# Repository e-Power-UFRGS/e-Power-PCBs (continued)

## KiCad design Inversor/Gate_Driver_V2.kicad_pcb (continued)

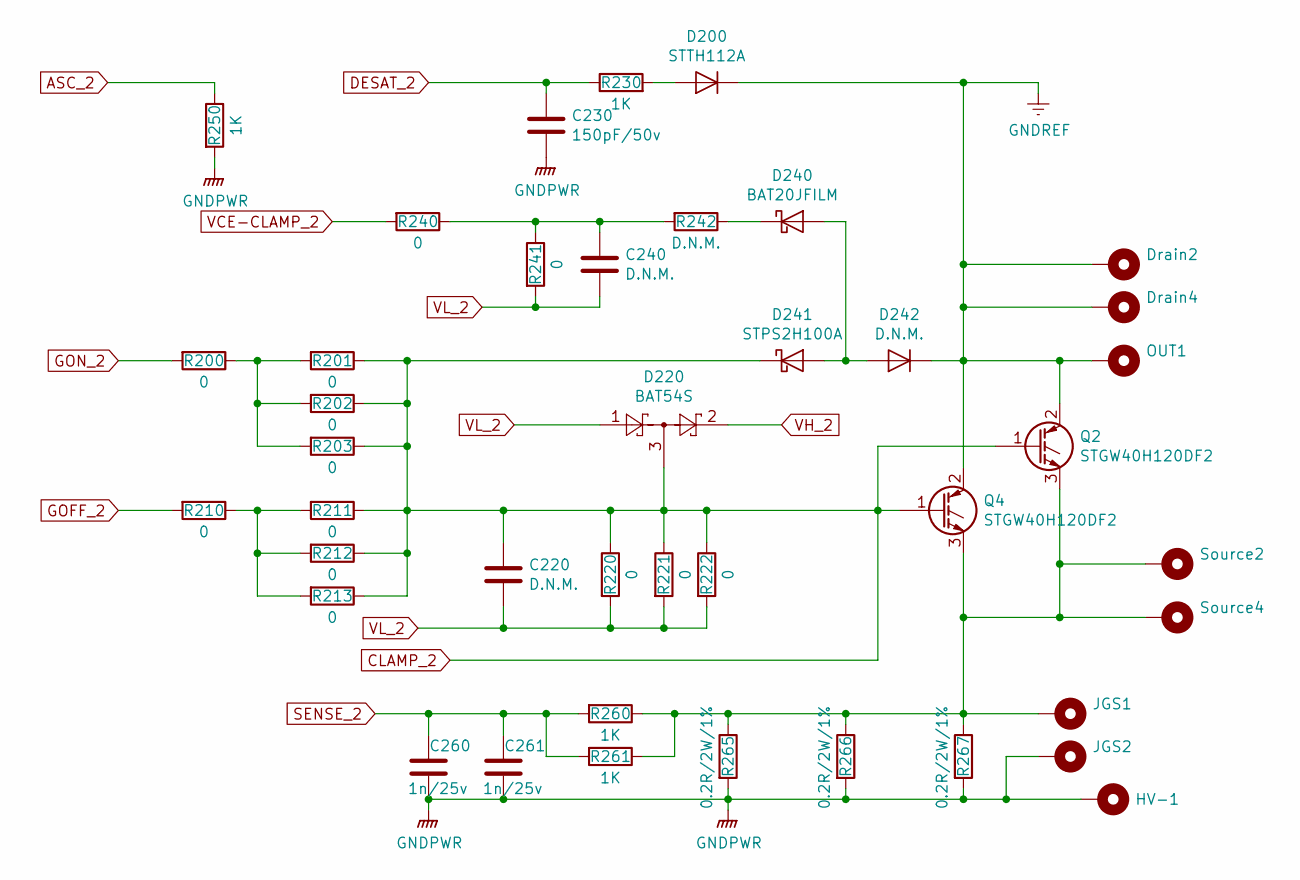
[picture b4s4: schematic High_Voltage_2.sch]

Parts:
C220, C240: D.N.M.; C_0805_2012Metric
C230: 150pF/50v; C_0805_2012Metric
C260, C261: 1n/25v; C_0805_2012Metric
D200: STTH112A; D_SMA
D220: BAT54S; SOT-23
D240: BAT20JFILM; DO-214AC
D241: STPS2H100A; DO-214AC
D242: D.N.M.; D_SMA
Drain2, Drain4: MountingHole_Pad; MountingHole_2.2mm_M2_DIN965_Pad
HV-1: MountingHole_Pad; MountingHole_4.5mm_Pad
JGS1, JGS2: MountingHole_Pad; MountingHole_2.2mm_M2_DIN965_Pad
OUT1: MountingHole_Pad; MountingHole_4.5mm_Pad
Q1, Q2: STGW40H120DF2; TO-247-3_Vertical
R200, R201, R202, R203, R210, R211, R212, R213, R220, R221, R222, R240, R241: 0; R_0805_2012Metric
R230, R250, R260, R261: 1K; R_0805_2012Metric
R242: D.N.M.; R_0805_2012Metric
R265, R266, R267: 0.2R/2W/1%; R_2512_6332Metric
Source2, Source4: MountingHole_Pad; MountingHole_2.2mm_M2_DIN965_Pad

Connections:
ASC_2: R250.1; also elsewhere on the board
DESAT_2: C230.1, R230.1; also elsewhere on the board
GND_ISO_2: C230.2, C260.2, C261.2, HV-1.1, JGS2.1, R250.2, R265.2, R266.2, R267.2; also elsewhere on the board
GOFF_2: R210.2; also elsewhere on the board
GON_2: R200.2; also elsewhere on the board
unnamed: C240.1, R240.1, R241.1, R242.2
unnamed: D240.1 (K), R242.1
unnamed: D240.2 (A), D241.2 (A), D242.2 (A)
unnamed 27: D200.2 (A), R230.2; also elsewhere on the board
unnamed: R200.1, R201.2, R202.2, R203.2
unnamed: R210.1, R211.2, R212.2, R213.2
SENSE_2: C260.1, C261.1, R260.2, R261.2; also elsewhere on the board
VCE-CLAMP_2: R240.2; also elsewhere on the board
VH_2: D220.2; also elsewhere on the board
VL_2: C220.2, C240.2, D220.1, R220.2, R221.2, R222.2, R241.2; also elsewhere on the board

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
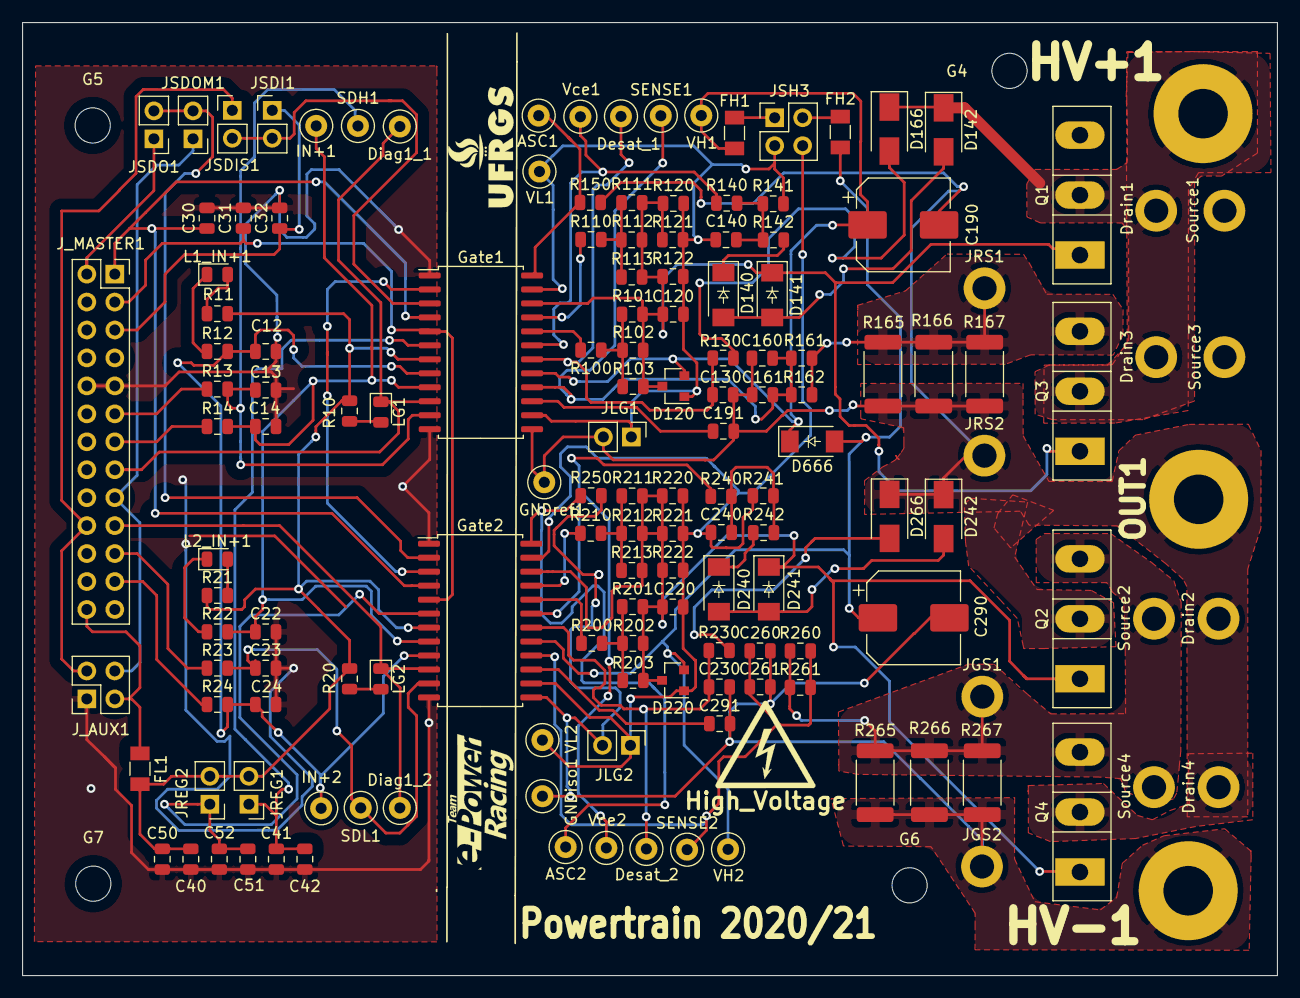
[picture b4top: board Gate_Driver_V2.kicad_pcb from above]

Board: 2 copper layers, 114.0 x 86.6 mm, 158 parts (0 on the bottom side), 69 nets.

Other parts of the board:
D166, D266: STTH112A; D_SMA
Q4: STGW40H120DF2; TO-247-3_Vertical

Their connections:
unnamed 24: D166.2; also elsewhere on the board
unnamed 27: D266.2; also elsewhere on the board

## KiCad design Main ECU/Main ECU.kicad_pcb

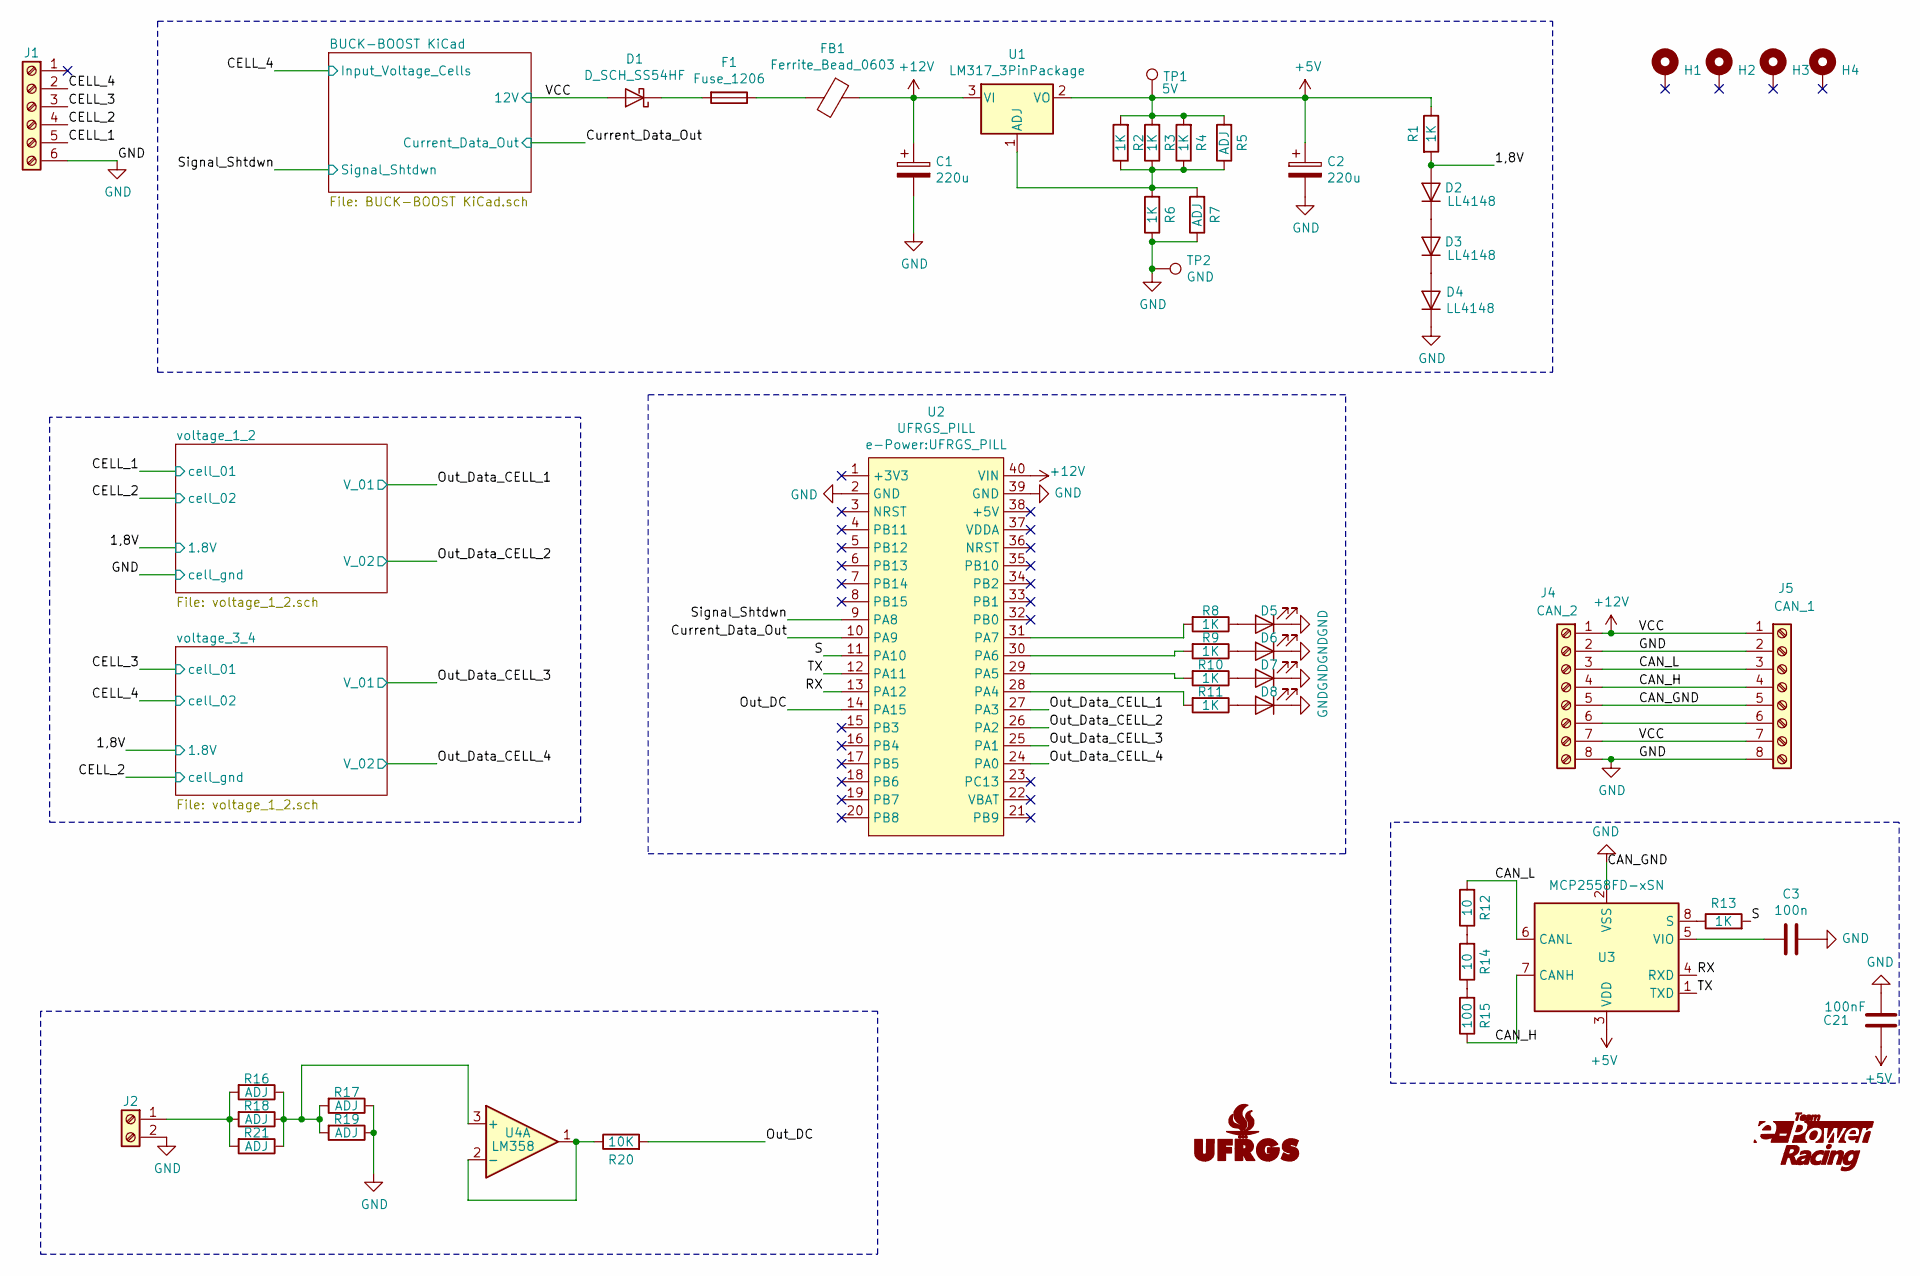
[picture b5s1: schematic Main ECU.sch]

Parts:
C1, C2: 220u; CP_Elec_10x10
C3: 100n; C_0805_2012Metric
C21: 100nF; C_0805_2012Metric
D1: D_SCH_SS54HF; DO-214AC; LCSC C22452
D2, D3, D4: LL4148; SOD-80
D5, D6, D7, D8: LED; LED_0805_1.15x1.40mm_HandSolder
F1: Fuse_1206; FUSE_1206_3216Metric
FB1: Ferrite_Bead_0603; FB_0805_2012Metric
G1: Logo_UFRGS_Large; Logo_UFRGS_14.7x8.0mm_SilkS
G2: Logo_e-Power_Large; Logo_e-Power_16.5x8.0mm_SilkS
H1, H2, H3, H4: MountingHole_Pad; MountingHole_3.2mm_M3_Pad_Via
J1: Screw_Terminal_01x06; PhoenixContact_MSTBA_2,5_6-G-5,08_1x06_P5.08mm_Horizontal
J2: Screw_Terminal_01x02; TerminalBlock_Phoenix_MKDS-1,5-2_1x02_P5.08mm_Horizontal_3D
J4: CAN_2; Molex_Mini-Fit_Jr_2x04_P4.20mm_Horizontal
J5: CAN_1; Molex_Mini-Fit_Jr_2x04_P4.20mm_Horizontal
R1, R2, R3, R4, R6, R8, R9, R10, R11, R13: 1K; R_0805_2012Metric
R5, R7, R16, R17, R18, R19, R21: ADJ; R_0805_2012Metric
R12, R14: 10; R_0805_2012Metric
R15: 100; R_0805_2012Metric
R20: 10K; R_0805_2012Metric
TP1: 5V; TestPoint_Pad_D1.0mm
TP2: GND; TestPoint_Pad_D1.0mm
U1: LM317_3PinPackage; TO-220-3_Horizontal_TabDown
U2: UFRGS_PILL
U3: MCP2558FD-xSN; SOIC-8_3.9x4.9mm_P1.27mm
U4: LM358; SOIC-8_3.9x4.9mm_P1.27mm

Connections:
+5V: C2.1, C21.1, R1.1, R2.2, R3.2, R4.2, R5.2, TP1.1, U1.2 (VO), U3.3 (VDD)
+12V: C1.1, D1.2 (A), FB1.1, J4.1, J4.7, J5.1, J5.7, U1.3 (VI), U2.40 (VIN); also elsewhere on the board
/1,8V: D2.2 (A), R1.2; also elsewhere on the board
/CAN_H: J4.4, J5.4, R15.1, U3.7 (CANH)
/CAN_L: J4.3, J5.3, R12.2, U3.6 (CANL)
/CELL_1: J1.5; also elsewhere on the board
/CELL_2: J1.4; also elsewhere on the board
/CELL_3: J1.3; also elsewhere on the board
/CELL_4: J1.2; also elsewhere on the board
/Current_Data_Out: U2.10 (PA9); also elsewhere on the board
/Out_DC: R20.2, U2.14 (PA15)
/Out_Data_CELL_1: U2.27 (PA3); also elsewhere on the board
/Out_Data_CELL_2: U2.26 (PA2); also elsewhere on the board
/Out_Data_CELL_3: U2.25 (PA1); also elsewhere on the board
/Out_Data_CELL_4: U2.24 (PA0); also elsewhere on the board
/RX: U2.13 (PA12), U3.4 (RXD)
/S: R13.2, U2.11 (PA10)
/Signal_Shtdwn: U2.9 (PA8); also elsewhere on the board
/TX: U2.12 (PA11), U3.1 (TXD)
GND: C1.2, C2.2, C3.1, C21.2, D4.1 (K), D5.1 (K), D6.1 (K), D7.1 (K), D8.1 (K), J1.6, J2.2, J4.2, J4.5, J4.8, J5.2, J5.5, J5.8, R6.1, R7.1, R17.1, R19.1, TP2.1, U2.2 (GND), U2.39 (GND), U3.2 (VSS); also elsewhere on the board
unnamed: C3.2, U3.5 (VIO)
unnamed: D1.1 (K), F1.2
unnamed: D2.1 (K), D3.2 (A)
unnamed: D3.1 (K), D4.2 (A)
unnamed: D5.2 (A), R8.1
unnamed: D6.2 (A), R9.1
unnamed: D7.2 (A), R10.1
unnamed: D8.2 (A), R11.1
unnamed: F1.1, FB1.2
unnamed: J2.1, R16.2, R18.2, R21.2
unnamed: J4.6, J5.6
unnamed: R2.1, R3.1, R4.1, R5.1, R6.2, R7.2, U1.1 (ADJ)
unnamed: R8.2, U2.31 (PA7)
unnamed: R9.2, U2.30 (PA6)
unnamed: R10.2, U2.29 (PA5)
unnamed: R11.2, U2.28 (PA4)
unnamed: R12.1, R14.2
unnamed: R13.1, U3.8 (S)
unnamed: R14.1, R15.2
unnamed: R16.1, R17.2, R18.1, R19.2, R21.1, U4.3 (+)
unnamed: R20.1, U4.1, U4.2 (-)

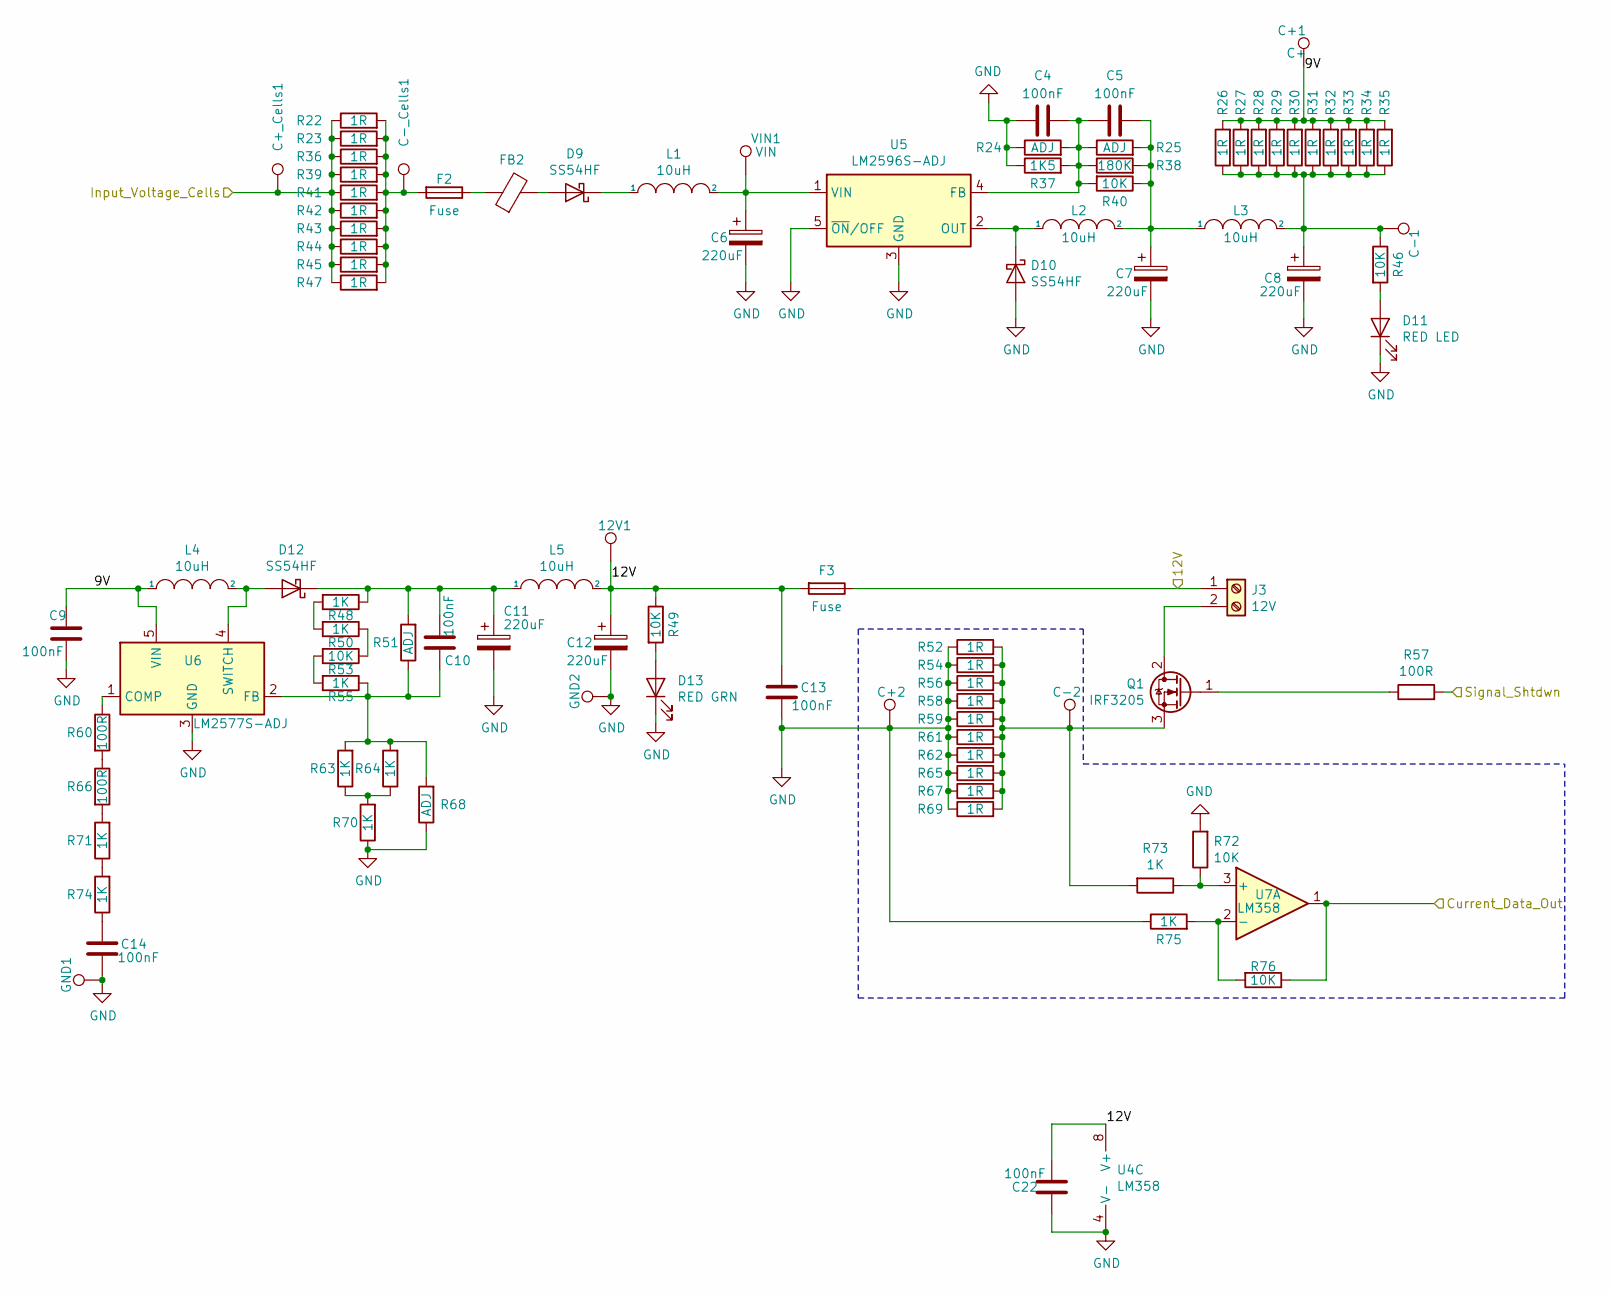
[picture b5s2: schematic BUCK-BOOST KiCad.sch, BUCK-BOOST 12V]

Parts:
12V1: 12V; TestPoint_Pad_D1.0mm
C4, C5, C9, C10, C13, C14, C22: 100nF; C_0805_2012Metric
C6, C7, C8, C11, C12: 220uF; CP_Elec_10x10
C+1, C+2: C+; TestPoint_Pad_D1.0mm
C+_Cells1: C+_Cells; TestPoint_Pad_D1.0mm
C-1, C-2: C-; TestPoint_Pad_D1.0mm
C-_Cells1: C-_Cells; TestPoint_Pad_D1.0mm
D9, D10, D12: SS54HF; DO-214AC
D11: RED LED; LED_0805_1.15x1.40mm_HandSolder
D13: RED GRN; LED_0805_1.15x1.40mm_HandSolder
F2, F3: Fuse; FUSE_1206_3216Metric
FB2: Ferrite_Bead_0603; FB_0805_2012Metric
GND1, GND2: GND; TestPoint_Pad_D1.0mm
J3: 12V; TerminalBlock_Phoenix_MKDS-1,5-2_1x02_P5.08mm_Horizontal_3D
L1, L2, L3, L4, L5: 10uH; L_12x12mm_H6mm
Q1: IRF3205; TO-220-3_Horizontal_TabDown
R22, R23, R26, R27, R28, R29, R30, R31, R32, R33, R34, R35, R36, R39, R41, R42, R43, R44, R45, R47, R52, R54, R56, R58, R59, R61, R62, R65, R67, R69: 1R; R_0805_2012Metric
R24, R25, R51, R68: ADJ; R_0805_2012Metric
R37: 1K5; R_0805_2012Metric
R38: 180K; R_0805_2012Metric
R40, R46, R49, R53, R72, R76: 10K; R_0805_2012Metric
R48, R50, R55, R63, R64, R70, R71, R73, R74, R75: 1K; R_0805_2012Metric
R57, R60, R66: 100R; R_0805_2012Metric
U4: LM358
U5: LM2596S-ADJ; TO-263-5_TabPin3
U6: LM2577S-ADJ; TO-263-5_TabPin3
U7: LM358; SOIC-8_3.9x4.9mm_P1.27mm
VIN1: VIN; TestPoint_Pad_D1.0mm

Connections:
+12V: 12V1.1, C12.1, C13.2, C22.2, F3.1, F3.2, J3.1, L5.2, R49.1, U4.8 (V+); also elsewhere on the board
/BUCK-BOOST KiCad/9V: C9.2, C+1.1, L4.1, R26.2, R27.2, R28.2, R29.2, R30.2, R31.2, R32.2, R33.2, R34.2, R35.2, U6.5 (VIN)
/CELL_4: C+_Cells1.1, R22.1, R23.1, R36.1, R39.1, R41.1, R42.1, R43.1, R44.1, R45.1, R47.1; also elsewhere on the board
/Current_Data_Out: R76.1, U7.1; also elsewhere on the board
/Signal_Shtdwn: R57.2; also elsewhere on the board
GND: C4.2, C6.2, C7.2, C8.2, C9.1, C11.2, C12.2, C13.1, C14.1, C22.1, C+2.1, D10.2 (A), D11.1 (K), D13.1 (K), GND1.1, GND2.1, R24.1, R37.1, R52.1, R54.1, R56.1, R58.1, R59.1, R61.1, R62.1, R65.1, R67.1, R68.1, R69.1, R70.1, R72.2, R75.1, U4.4 (V-), U5.3 (GND), U5.5 (~ON~/OFF), U6.3 (GND); also elsewhere on the board
unnamed: C4.1, C5.2, R24.2, R25.1, R37.2, R38.1, R40.2, U5.4 (FB)
unnamed: C5.1, C7.1, L2.2, L3.1, R25.2, R38.2, R40.1
unnamed: C6.1, L1.2, U5.1 (VIN), VIN1.1
unnamed: C10.1, R51.1, R55.1, R63.2, R64.2, R68.2, U6.2 (FB)
unnamed: C10.2, C11.1, D12.1 (K), L5.1, R48.1, R51.2
unnamed: C14.2, R74.1
unnamed: C8.1, C-1.1, L3.2, R26.1, R27.1, R28.1, R29.1, R30.1, R31.1, R32.1, R33.1, R34.1, R35.1, R46.1
unnamed: C-2.1, Q1.3 (S), R52.2, R54.2, R56.2, R58.2, R59.2, R61.2, R62.2, R65.2, R67.2, R69.2, R73.2
unnamed: C-_Cells1.1, F2.2, R22.2, R23.2, R36.2, R39.2, R41.2, R42.2, R43.2, R44.2, R45.2, R47.2
unnamed: D9.1 (K), L1.1
unnamed: D9.2 (A), FB2.2
unnamed: D10.1 (K), L2.1, U5.2 (OUT)
unnamed: D11.2 (A), R46.2
unnamed: D12.2 (A), L4.2, U6.4 (SWITCH)
unnamed: D13.2 (A), R49.2
unnamed: F2.1, FB2.1
unnamed: J3.2, Q1.2 (D)
unnamed: Q1.1 (G), R57.1
unnamed: R48.2, R50.2
unnamed: R50.1, R53.1
unnamed: R53.2, R55.2
unnamed: R60.1, U6.1 (COMP)
unnamed: R60.2, R66.1
unnamed: R63.1, R64.1, R70.2
unnamed: R66.2, R71.2
unnamed: R71.1, R74.2
unnamed: R72.1, R73.1, U7.3 (+)
unnamed: R75.2, R76.2, U7.2 (-)

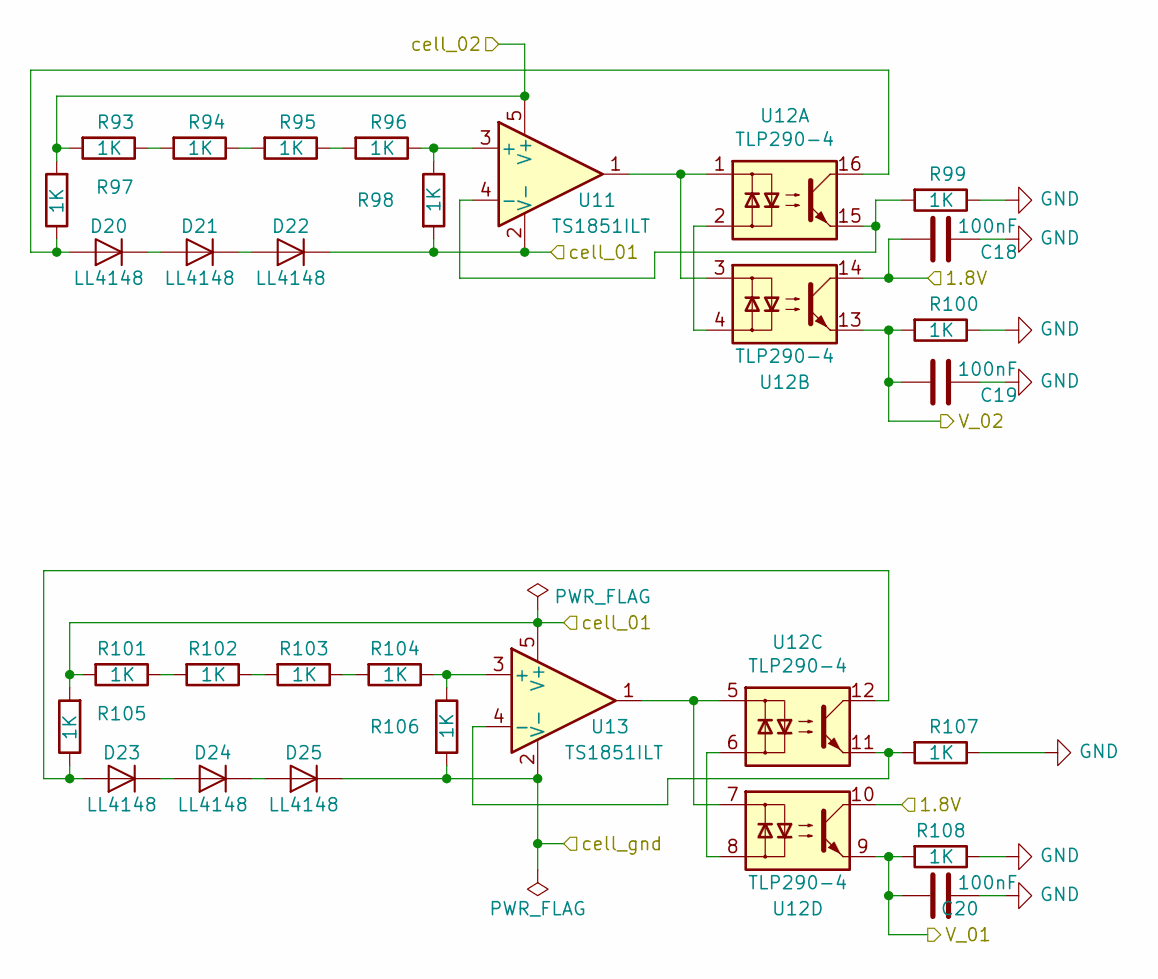
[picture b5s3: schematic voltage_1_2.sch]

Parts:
C15, C16, C17: 100nF; C_0805_2012Metric; Voltage 50V; LCSC C49678
D14, D15, D16, D17, D18, D19: LL4148; SOD-80
R77, R78, R79, R80, R81, R82, R83, R84, R85, R86, R87, R88, R89, R90, R91, R92: 1K; R_0805_2012Metric; Voltage 150V; LCSC C17513
U8, U10: TS1851ILT; SOT-23-5_HandSoldering
U9: TLP290-4; SOIC-16_4.55x10.3mm_P1.27mm(TLP290-4)

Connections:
/1,8V: C15.1, U9.10, U9.14; also elsewhere on the board
/CELL_1: D16.1 (K), R82.2, R85.2, R89.2, U8.2 (V-), U10.5 (V+); also elsewhere on the board
/CELL_2: R77.2, R81.2, U8.5 (V+); also elsewhere on the board
/Out_Data_CELL_1: C17.1, R92.2, U9.9; also elsewhere on the board
/Out_Data_CELL_2: C16.1, R84.2, U9.13; also elsewhere on the board
GND: C15.2, C16.2, C17.2, D19.1 (K), R83.1, R84.1, R90.2, R91.1, R92.1, U10.2 (V-); also elsewhere on the board
unnamed: D14.1 (K), D15.2 (A)
unnamed: D14.2 (A), R81.1, U9.16
unnamed: D15.1 (K), D16.2 (A)
unnamed: D17.1 (K), D18.2 (A)
unnamed: D17.2 (A), R89.1, U9.12
unnamed: D18.1 (K), D19.2 (A)
unnamed: R77.1, R78.2
unnamed: R78.1, R79.2
unnamed: R79.1, R80.2
unnamed: R80.1, R82.1, U8.3 (+)
unnamed: R83.2, U8.4 (-), U9.15
unnamed: R85.1, R86.2
unnamed: R86.1, R87.2
unnamed: R87.1, R88.2
unnamed: R88.1, R90.1, U10.3 (+)
unnamed: R91.2, U9.11, U10.4 (-)
unnamed: U8.1, U9.1, U9.3
unnamed: U9.2, U9.4
unnamed: U9.6, U9.8
unnamed: U9.5, U9.7, U10.1

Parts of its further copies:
C18, C19, C20: 100nF; C_0805_2012Metric; Voltage 50V; LCSC C49678
D20, D21, D22, D23, D24, D25: LL4148; SOD-80
R93, R94, R95, R96, R97, R98, R99, R100, R101, R102, R103, R104, R105, R106, R107, R108: 1K; R_0805_2012Metric; Voltage 150V; LCSC C17513
U11, U13: TS1851ILT; SOT-23-5_HandSoldering
U12: TLP290-4; SOIC-16_4.55x10.3mm_P1.27mm(TLP290-4)

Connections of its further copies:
/1,8V: C18.1, U12.10, U12.14; also elsewhere on the board
/CELL_2: D25.1 (K), R106.2, U13.2 (V-); also elsewhere on the board
/CELL_3: D22.1 (K), R98.2, R101.2, R105.2, U11.2 (V-), U13.5 (V+); also elsewhere on the board
/CELL_4: R93.2, R97.2, U11.5 (V+); also elsewhere on the board
/Out_Data_CELL_3: C20.1, R108.2, U12.9; also elsewhere on the board
/Out_Data_CELL_4: C19.1, R100.2, U12.13; also elsewhere on the board
GND: C18.2, C19.2, C20.2, R99.1, R100.1, R107.1, R108.1; also elsewhere on the board
unnamed: D20.1 (K), D21.2 (A)
unnamed: D20.2 (A), R97.1, U12.16
unnamed: D21.1 (K), D22.2 (A)
unnamed: D23.1 (K), D24.2 (A)
unnamed: D23.2 (A), R105.1, U12.12
unnamed: D24.1 (K), D25.2 (A)
unnamed: R93.1, R94.2
unnamed: R94.1, R95.2
unnamed: R95.1, R96.2
unnamed: R96.1, R98.1, U11.3 (+)
unnamed: R99.2, U11.4 (-), U12.15
unnamed: R101.1, R102.2
unnamed: R102.1, R103.2
unnamed: R103.1, R104.2
unnamed: R104.1, R106.1, U13.3 (+)
unnamed: R107.2, U12.11, U13.4 (-)
unnamed: U11.1, U12.1, U12.3
unnamed: U12.2, U12.4
unnamed: U12.5, U12.7, U13.1
unnamed: U12.6, U12.8

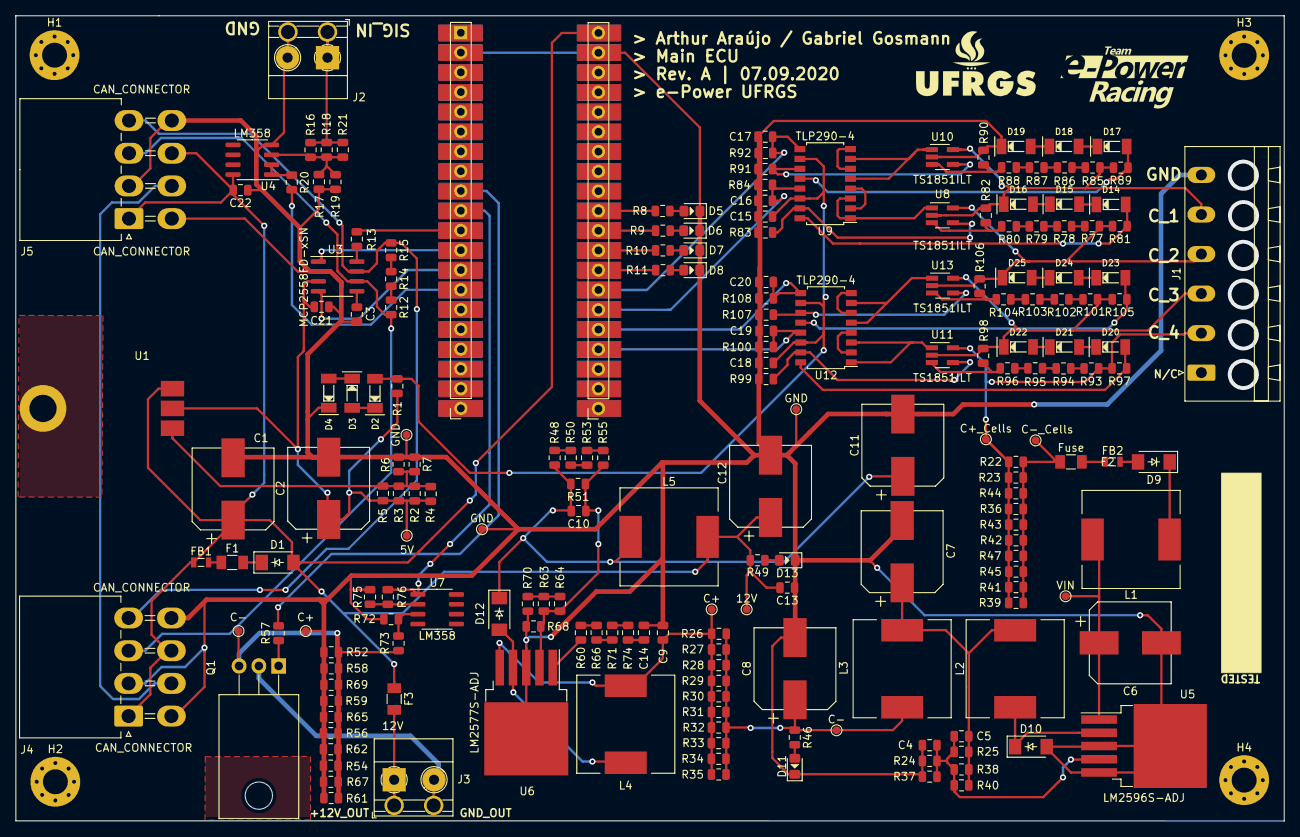
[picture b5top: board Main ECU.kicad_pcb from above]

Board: 2 copper layers, 163.0 x 103.4 mm, 202 parts (0 on the bottom side), 110 nets.

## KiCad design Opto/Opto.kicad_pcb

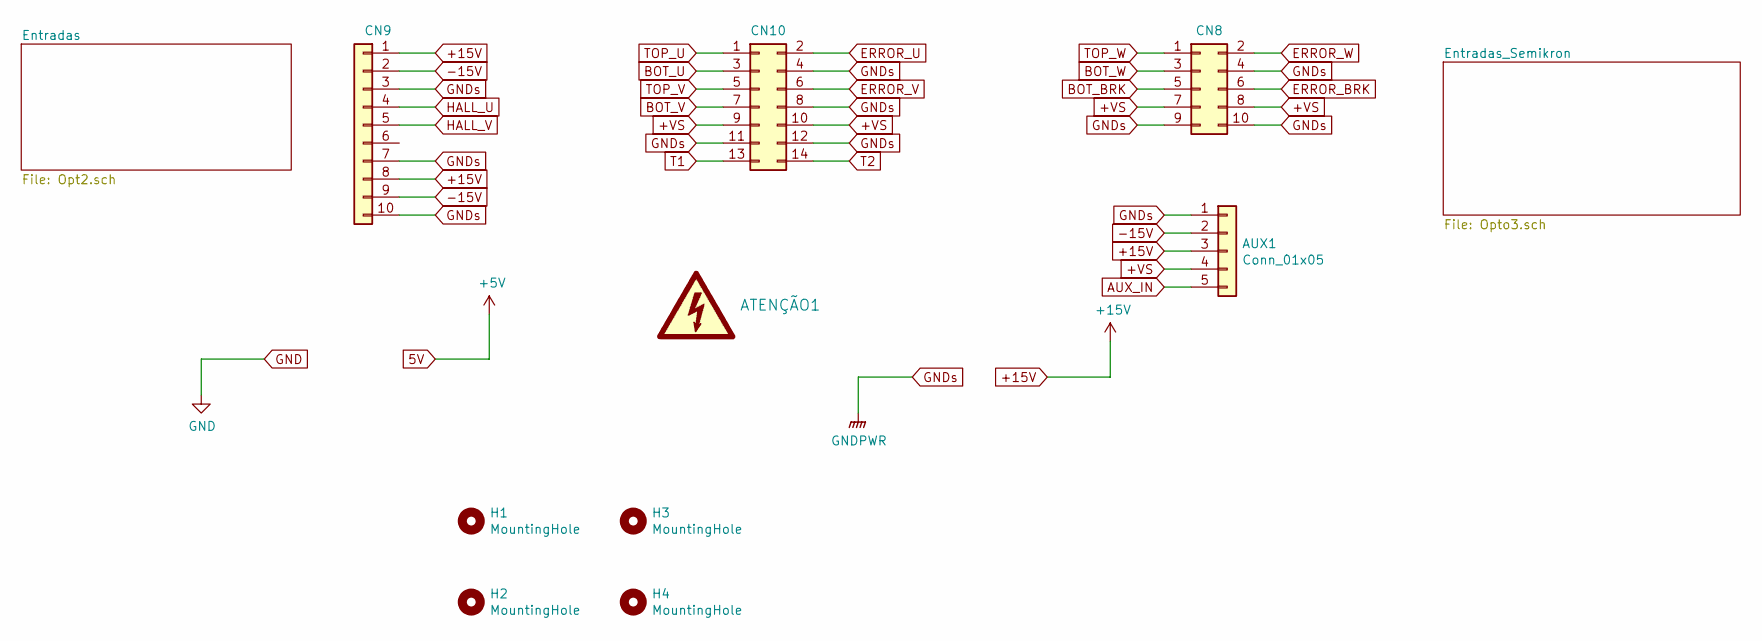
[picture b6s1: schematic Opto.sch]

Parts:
ATENÇÃO1: Logo_High_Voltage_Large; Logo_High_Voltage_9.1x8.0mm_SilkS
AUX1: Conn_01x05; PinSocket_1x05_P2.54mm_Vertical
CN8: Conn_02x05_Odd_Even; PinSocket_2x05_P2.54mm_Vertical
CN9: Conn_01x10; PinSocket_1x10_P2.54mm_Vertical
CN10: Conn_02x07_Odd_Even; PinSocket_2x07_P2.54mm_Vertical
H1, H2, H3, H4: MountingHole; MountingHole_2.2mm_M2

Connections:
+15V: AUX1.3, CN9.1, CN9.8; also elsewhere on the board
+VS: AUX1.4, CN8.7, CN8.8, CN10.9, CN10.10
-15V: AUX1.2, CN9.2, CN9.9
AUX_IN: AUX1.5; also elsewhere on the board
BOT_BRK: CN8.5; also elsewhere on the board
BOT_U: CN10.3; also elsewhere on the board
BOT_V: CN10.7; also elsewhere on the board
BOT_W: CN8.3; also elsewhere on the board
ERROR_BRK: CN8.6; also elsewhere on the board
ERROR_U: CN10.2; also elsewhere on the board
ERROR_V: CN10.6; also elsewhere on the board
ERROR_W: CN8.2; also elsewhere on the board
GNDs: AUX1.1, CN8.4, CN8.9, CN8.10, CN9.3, CN9.7, CN9.10, CN10.4, CN10.8, CN10.11, CN10.12; also elsewhere on the board
HALL_U: CN9.4; also elsewhere on the board
HALL_V: CN9.5; also elsewhere on the board
T1: CN10.13; also elsewhere on the board
T2: CN10.14; also elsewhere on the board
TOP_U: CN10.1; also elsewhere on the board
TOP_V: CN10.5; also elsewhere on the board
TOP_W: CN8.1; also elsewhere on the board

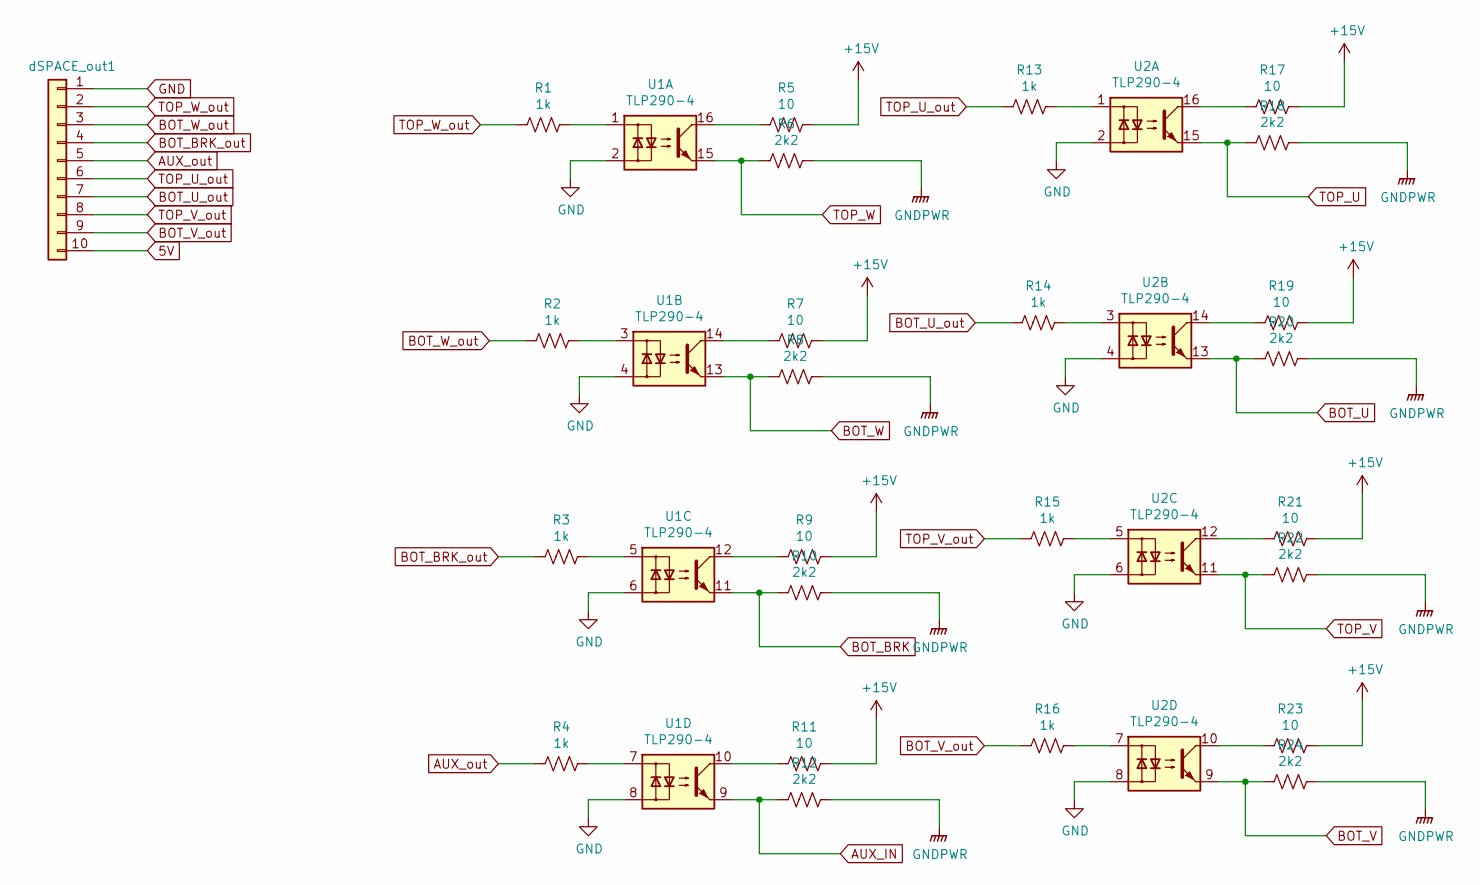
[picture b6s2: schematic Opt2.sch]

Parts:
R1, R2, R3, R4, R13, R14, R15, R16: 1k; R_Axial_DIN0204_L3.6mm_D1.6mm_P5.08mm_Horizontal
R5, R7, R9, R11, R17, R19, R21, R23: 10; R_Axial_DIN0204_L3.6mm_D1.6mm_P5.08mm_Horizontal
R6, R8, R10, R12, R18, R20, R22, R24: 2k2; R_Axial_DIN0204_L3.6mm_D1.6mm_P5.08mm_Horizontal
U1, U2: TLP290-4; SOP-16_4.55x10.3mm_P1.27mm
dSPACE_out1: Conn_01x10; PinHeader_1x10_P2.54mm_Vertical

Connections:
+15V: R5.1, R7.1, R9.1, R11.1, R17.1, R19.1, R21.1, R23.1; also elsewhere on the board
AUX_IN: R12.1, U1.9; also elsewhere on the board
AUX_out: R4.2, dSPACE_out1.5
BOT_BRK: R10.1, U1.11; also elsewhere on the board
BOT_BRK_out: R3.2, dSPACE_out1.4
BOT_U: R20.1, U2.13; also elsewhere on the board
BOT_U_out: R14.2, dSPACE_out1.7
BOT_V: R24.1, U2.9; also elsewhere on the board
BOT_V_out: R16.2, dSPACE_out1.9
BOT_W: R8.1, U1.13; also elsewhere on the board
BOT_W_out: R2.2, dSPACE_out1.3
GND: U1.2, U1.4, U1.6, U1.8, U2.2, U2.4, U2.6, U2.8, dSPACE_out1.1; also elsewhere on the board
GNDs: R6.2, R8.2, R10.2, R12.2, R18.2, R20.2, R22.2, R24.2; also elsewhere on the board
unnamed: R1.1, U1.1
unnamed: R2.1, U1.3
unnamed: R3.1, U1.5
unnamed: R4.1, U1.7
unnamed: R5.2, U1.16
unnamed: R7.2, U1.14
unnamed: R9.2, U1.12
unnamed: R11.2, U1.10
unnamed: R13.1, U2.1
unnamed: R14.1, U2.3
unnamed: R15.1, U2.5
unnamed: R16.1, U2.7
unnamed: R17.2, U2.16
unnamed: R19.2, U2.14
unnamed: R21.2, U2.12
unnamed: R23.2, U2.10
TOP_U: R18.1, U2.15; also elsewhere on the board
TOP_U_out: R13.2, dSPACE_out1.6
TOP_V: R22.1, U2.11; also elsewhere on the board
TOP_V_out: R15.2, dSPACE_out1.8
TOP_W: R6.1, U1.15; also elsewhere on the board
TOP_W_out: R1.2, dSPACE_out1.2

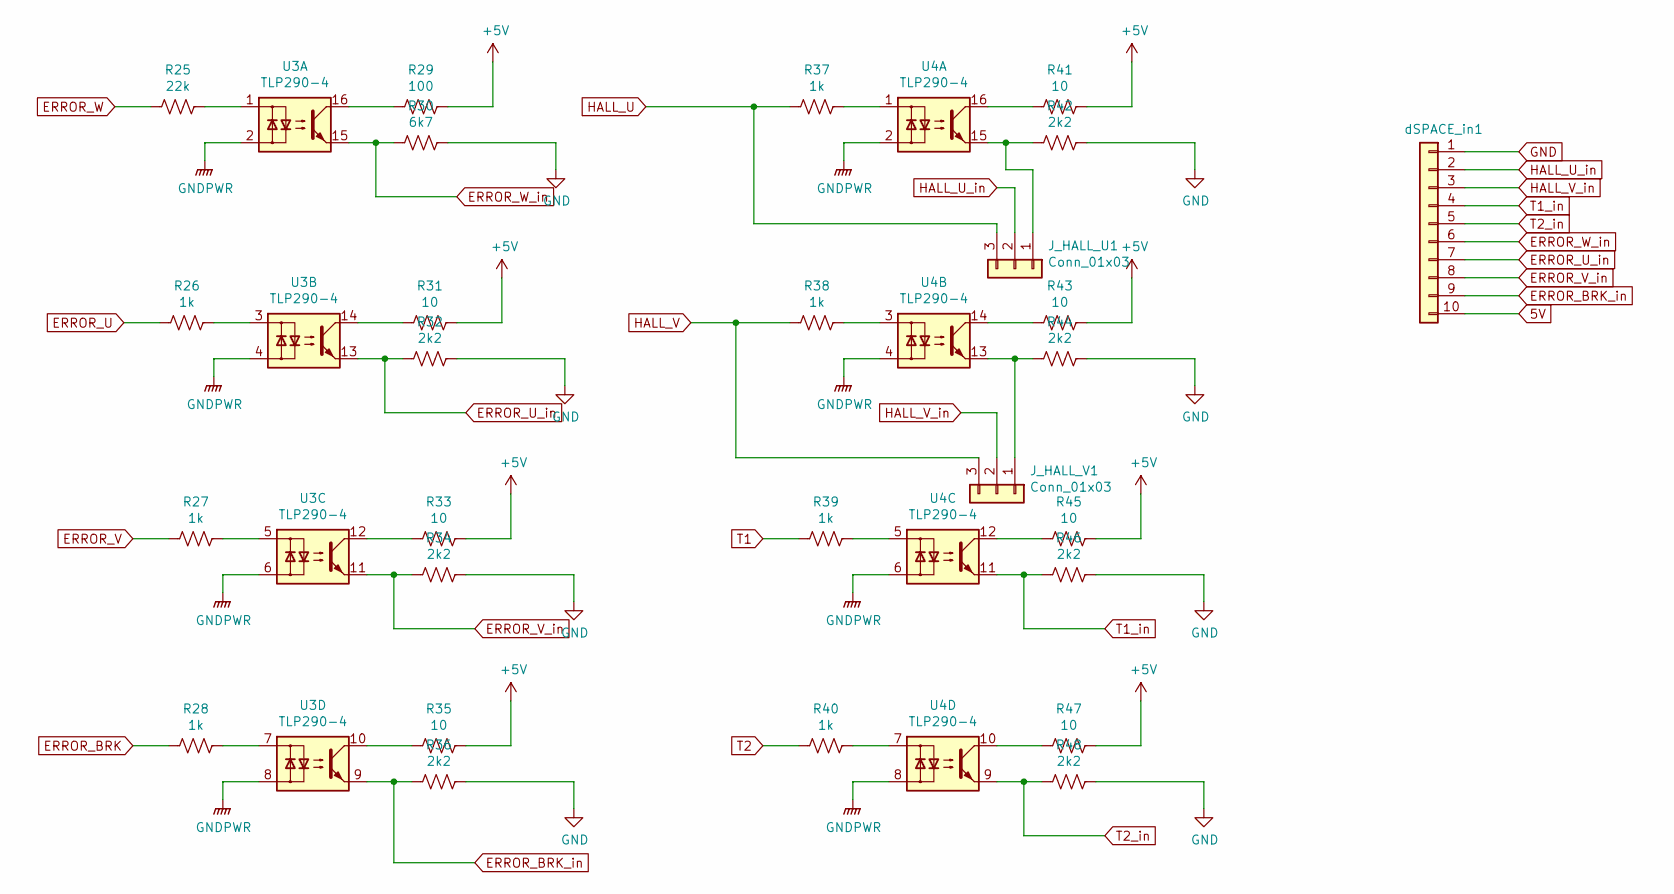
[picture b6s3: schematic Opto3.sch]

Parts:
J_HALL_U1: Conn_01x03; PinHeader_1x03_P2.54mm_Vertical
J_HALL_V1: Conn_01x03; PinHeader_1x03_P2.54mm_Vertical
R25: 22k; R_Axial_DIN0204_L3.6mm_D1.6mm_P5.08mm_Horizontal
R26, R27, R28, R37, R38, R39, R40: 1k; R_Axial_DIN0204_L3.6mm_D1.6mm_P5.08mm_Horizontal
R29: 100; R_Axial_DIN0204_L3.6mm_D1.6mm_P5.08mm_Horizontal
R30: 6k7; R_Axial_DIN0204_L3.6mm_D1.6mm_P5.08mm_Horizontal
R31, R33, R35, R41, R43, R45, R47: 10; R_Axial_DIN0204_L3.6mm_D1.6mm_P5.08mm_Horizontal
R32, R34, R36, R42, R44, R46, R48: 2k2; R_Axial_DIN0204_L3.6mm_D1.6mm_P5.08mm_Horizontal
U3, U4: TLP290-4; SOP-16_4.55x10.3mm_P1.27mm
dSPACE_in1: Conn_01x10; PinHeader_1x10_P2.54mm_Vertical

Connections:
ERROR_BRK: R28.2; also elsewhere on the board
ERROR_BRK_in: R36.1, U3.9, dSPACE_in1.9
ERROR_U: R26.2; also elsewhere on the board
ERROR_U_in: R32.1, U3.13, dSPACE_in1.7
ERROR_V: R27.2; also elsewhere on the board
ERROR_V_in: R34.1, U3.11, dSPACE_in1.8
ERROR_W: R25.2; also elsewhere on the board
ERROR_W_in: R30.1, U3.15, dSPACE_in1.6
GND: R30.2, R32.2, R34.2, R36.2, R42.2, R44.2, R46.2, R48.2, dSPACE_in1.1; also elsewhere on the board
GNDs: U3.2, U3.4, U3.6, U3.8, U4.2, U4.4, U4.6, U4.8; also elsewhere on the board
HALL_U: J_HALL_U1.3, R37.2; also elsewhere on the board
HALL_U_in: J_HALL_U1.2, dSPACE_in1.2
HALL_V: J_HALL_V1.3, R38.2; also elsewhere on the board
HALL_V_in: J_HALL_V1.2, dSPACE_in1.3
unnamed: J_HALL_U1.1, R42.1, U4.15
unnamed: J_HALL_V1.1, R44.1, U4.13
unnamed: R25.1, U3.1
unnamed: R26.1, U3.3
unnamed: R27.1, U3.5
unnamed: R28.1, U3.7
unnamed: R29.2, U3.16
unnamed: R31.2, U3.14
unnamed: R33.2, U3.12
unnamed: R35.2, U3.10
unnamed: R37.1, U4.1
unnamed: R38.1, U4.3
unnamed: R39.1, U4.5
unnamed: R40.1, U4.7
unnamed: R41.2, U4.16
unnamed: R43.2, U4.14
unnamed: R45.2, U4.12
unnamed: R47.2, U4.10
T1: R39.2; also elsewhere on the board
T1_in: R46.1, U4.11, dSPACE_in1.4
T2: R40.2; also elsewhere on the board
T2_in: R48.1, U4.9, dSPACE_in1.5

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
